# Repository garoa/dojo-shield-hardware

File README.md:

# dojo-shield-hardware

## Descrição
Arquivos de projeto de hardware do Garoa Dojo shield / Hardware design files for Garoa Dojo Arduino Shield

## Autoria
Projeto desenvolvido por Luciano Ramalho, Marcelo Rodrigues e time do Lab de Garagem.

## Hardware Livre
Este é um projeto de hardware livre e seus arquivos de design disposibilizados neste repositório estão licenciados sob os termos da licença Creative Commons BY-SA.

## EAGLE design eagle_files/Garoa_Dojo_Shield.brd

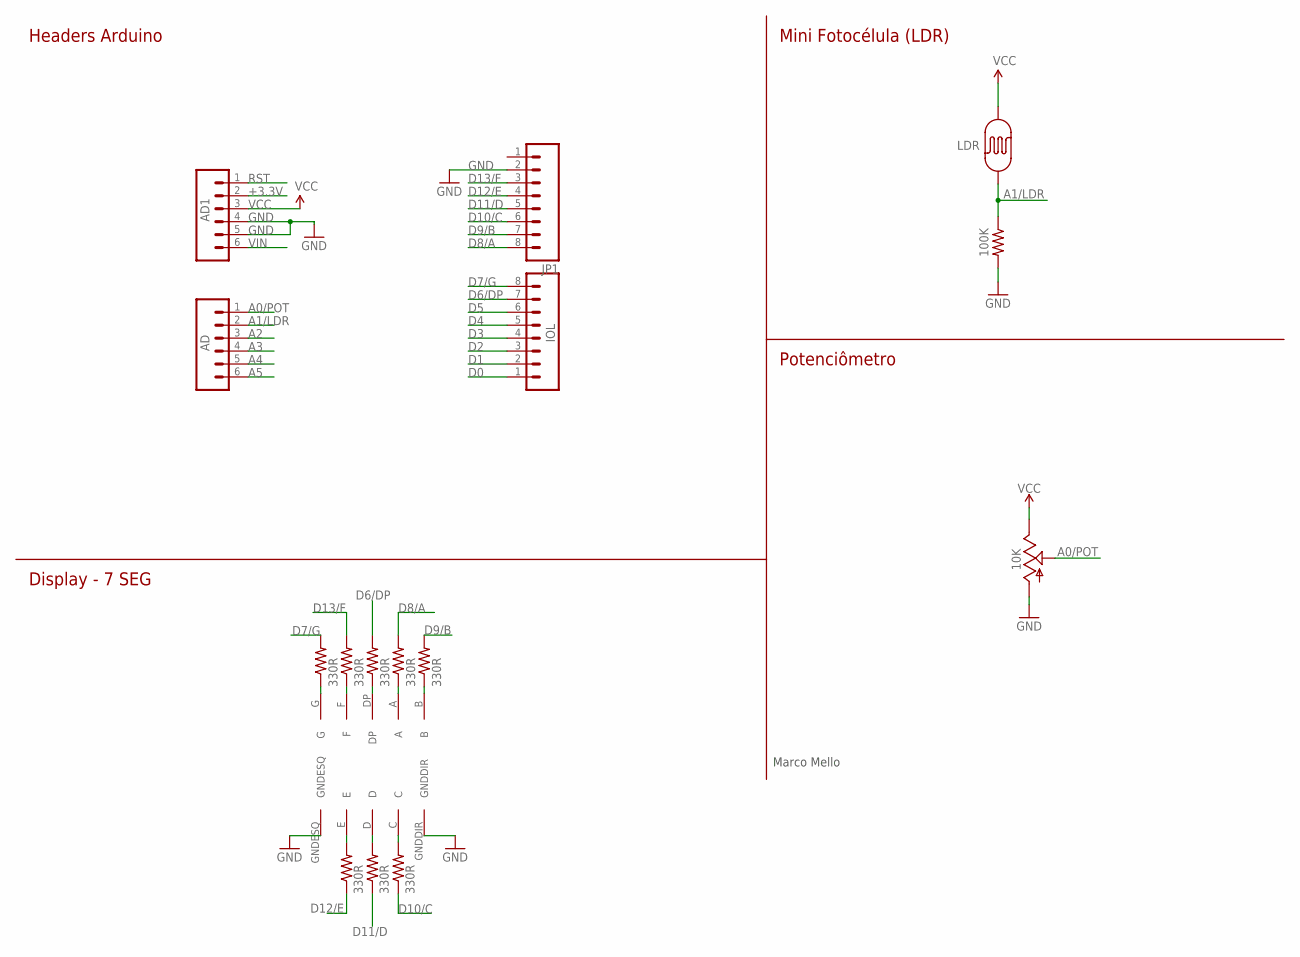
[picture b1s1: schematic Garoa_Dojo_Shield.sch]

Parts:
AD, AD1: M06SIP; 1X06
IOL: M08; 1X08
JP1: M081X08; 1X08
R1: LDR; PHOTOCELL
R2, R3, R4, R5, R6, R7, R8, R9: 330R; AXIAL-0.3-KIT
R10: 100K; AXIAL-0.3-KIT
U$1: 10K; POT_ALPHA_RV16AF-20
U$2: 7SEG-CODINGDOJO

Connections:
+3.3V: AD1.2
A0/POT: AD.1, U$1.2 (S)
A1/LDR: AD.2, R1.1, R10.P$1 (1)
A2: AD.3
A3: AD.4
A4: AD.5
A5: AD.6
D0: IOL.1
D1: IOL.2
D2: IOL.3
D3: IOL.4
D4: IOL.5
D5: IOL.6
D6/DP: IOL.7, R4.P$2 (2)
D7/G: IOL.8, R2.P$2 (2)
D8/A: JP1.8, R5.P$2 (2)
D9/B: JP1.7, R6.P$2 (2)
D10/C: JP1.6, R7.P$1 (1)
D11/D: JP1.5, R8.P$1 (1)
D12/E: JP1.4, R9.P$1 (1)
D13/F: JP1.3, R3.P$2 (2)
GND: AD1.4, AD1.5, JP1.2, R10.P$2 (2), U$1.1 (A), U$2.GNDDIR, U$2.GNDESQ
unnamed: R9.P$2 (2), U$2.E
unnamed: R8.P$2 (2), U$2.D
unnamed: R7.P$2 (2), U$2.C
unnamed: R2.P$1 (1), U$2.G
unnamed: R3.P$1 (1), U$2.F
unnamed: R4.P$1 (1), U$2.DP
unnamed: R5.P$1 (1), U$2.A
unnamed: R6.P$1 (1), U$2.B
RST: AD1.1
VCC: AD1.3, R1.2, U$1.3 (E)
VIN: AD1.6

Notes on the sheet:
Mini Fotocélula (LDR)
Headers Arduino
Display - 7 SEG
Potenciômetro
Marco Mello

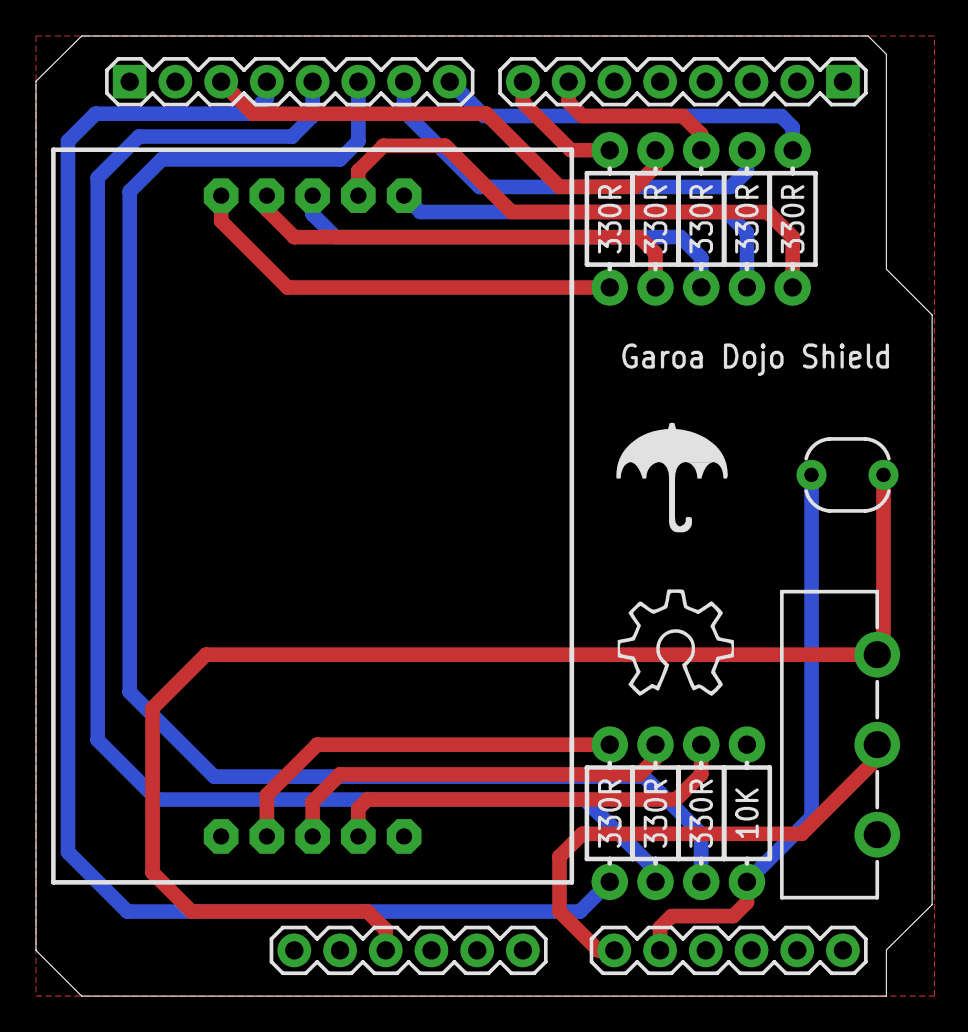
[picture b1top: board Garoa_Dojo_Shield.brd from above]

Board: 2 copper layers, 49.8 x 53.3 mm, 17 parts (0 on the bottom side), 20 nets.

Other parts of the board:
U$3: LDG-15MM

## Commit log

2016-02-19 zip contendo os arquivos de projeto como o pessoal do Lab de Garagem (Marcelo) nos passou autorizando a publicar sob CC-By-SA)
2016-02-19 descomprimindo os arquivos do ZIP (ainda precisamos arrumar os diretórios, posso fazer isso depois quando eu tiver mais tempo)
2016-02-19 aprimorando descrição e dando a devida atribuição de autoria e declaração de licenciamento como hardware livre
2016-02-19 Arrumando a casa...
2016-02-19 mais alguns pequenos ajustes
2016-02-19 renomeando (pra tirar o espaço do nome de arquivo)
2016-02-19 adicionando cabeçalho com autoria e licenciamento para o sketch de exemplo

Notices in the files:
parts and their libraries:
SparkFun-Sensors: Licensing: CC v3.0 Share-Alike You are welcome to use this library for commercial purposes.
